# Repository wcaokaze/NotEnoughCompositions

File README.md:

Not Enough Compositions
================================================================================

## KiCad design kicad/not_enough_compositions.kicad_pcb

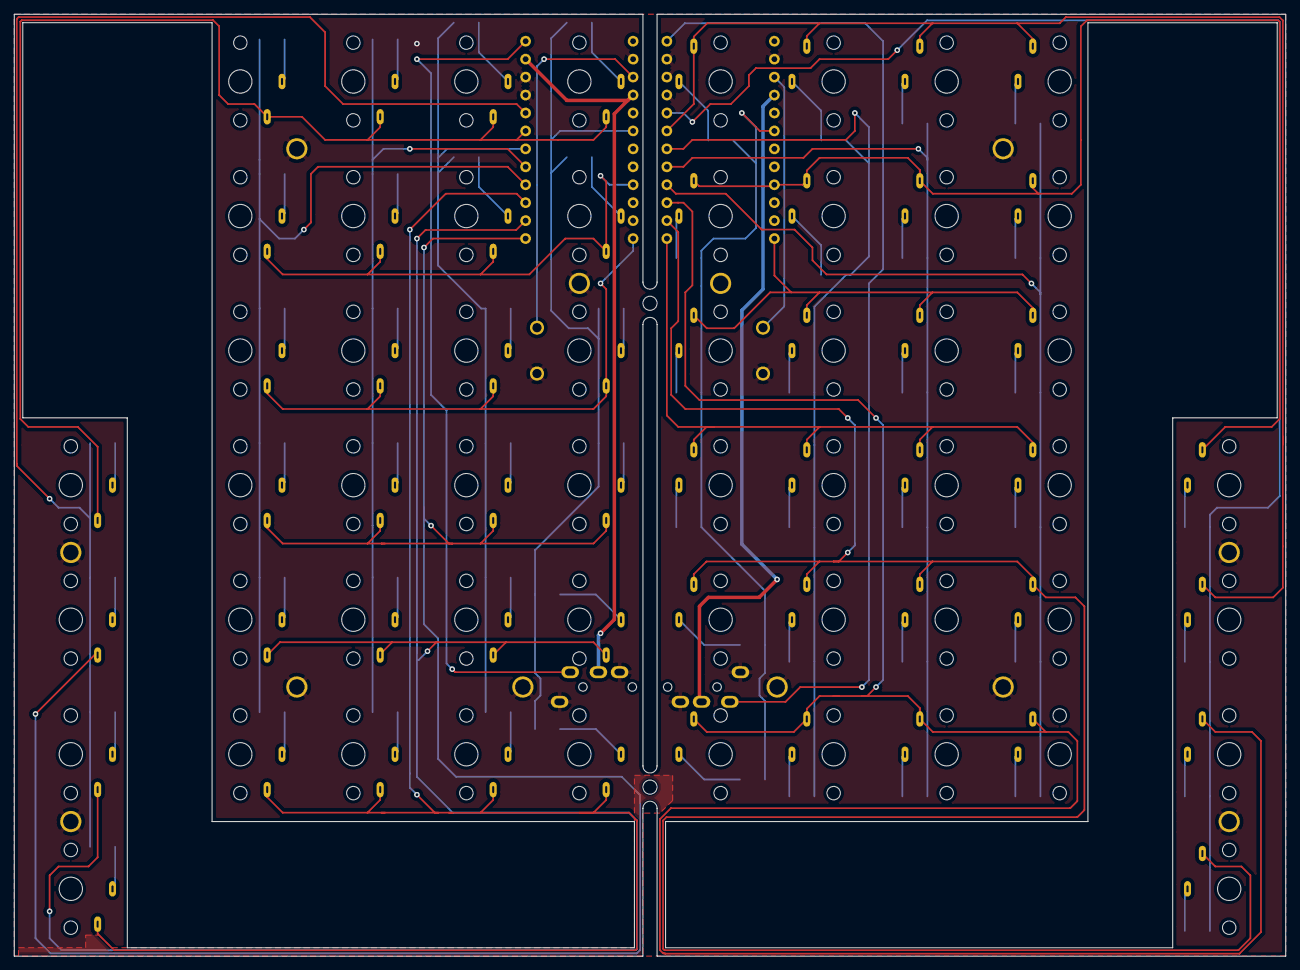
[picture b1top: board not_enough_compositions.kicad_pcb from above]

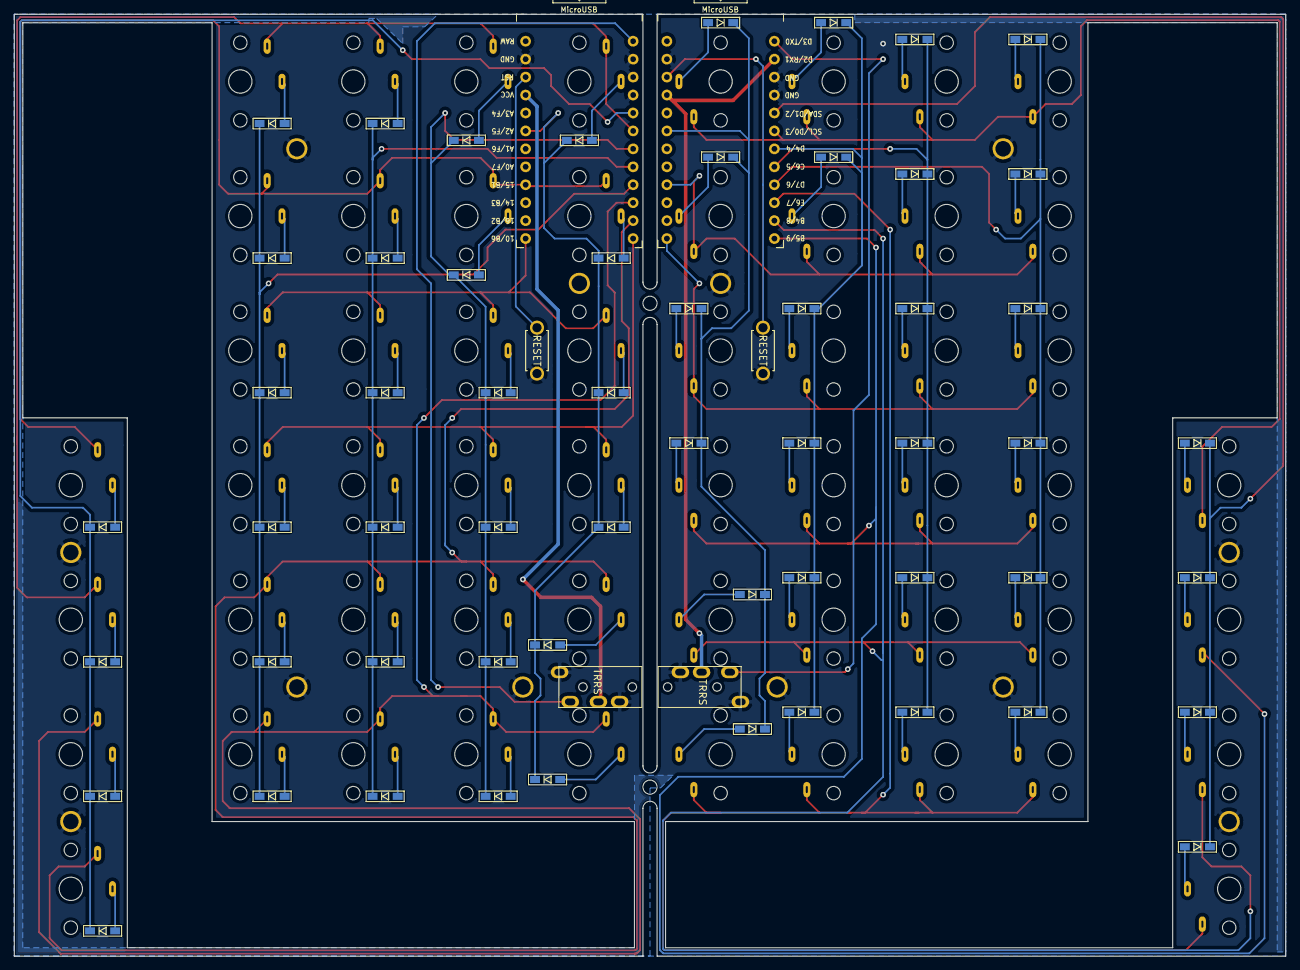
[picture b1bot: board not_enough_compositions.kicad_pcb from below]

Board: 2 copper layers, 180.0 x 133.3 mm, 118 parts (62 on the bottom side), 85 nets.

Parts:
D1, D2, D3, D4, D5, D6, D7, D8, D9, D10, D11, D12, D13, D14, D15, D16, D17, D18, D19, D20, D21, D22, D23, D24, D25, D26, D27, D28, D29, D30, D31, D32, D33, D34, D35, D36, D37, D38, D39, D40, D41, D42, D43, D44, D45, D46, D47, D48, D49, D50, D51, D52, D53, D54, D55, D56: D; D3_SMD_v2
J1, J2: MJ-4PP-9; MJ-4PP-9_1side
SW1, SW2: SW_PUSH; ResetSW_1side
SW3, SW4, SW5, SW6, SW7, SW8, SW9, SW10, SW11, SW12, SW13, SW14, SW15, SW16, SW17, SW18, SW19, SW20, SW21, SW22, SW23, SW24, SW25, SW26, SW27, SW28, SW29, SW30, SW31, SW32, SW33, SW34, SW35, SW36, SW37, SW38, SW39, SW40, SW41, SW42, SW43, SW44, SW45, SW46, SW47, SW48, SW49, SW50, SW51, SW52, SW53, SW54, SW55, SW56, SW57, SW58: SW_PUSH; choc_v1
U1, U2: ProMicro; ProMicro_v3.5

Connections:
GND: J1.A, J1.B, J2.A, J2.B, SW1.2, SW2.1, U1.3, U1.4, U1.23, U2.2, U2.3, U2.4, U2.23
unnamed: D1.2, SW3.2
unnamed: D2.2, SW4.2
unnamed: D3.2, SW5.2
unnamed: D4.2, SW6.2
unnamed: D5.2, SW7.2
unnamed: D6.2, SW8.2
unnamed: D7.2, SW9.2
unnamed: D8.2, SW10.2
unnamed: D9.2, SW11.2
unnamed: D10.2, SW12.2
unnamed: D11.2, SW13.2
unnamed: D12.2, SW14.2
unnamed: D13.2, SW15.2
unnamed: D14.2, SW16.2
unnamed: D15.2, SW17.2
unnamed: D16.2, SW18.2
unnamed: D17.2, SW19.2
unnamed: D18.2, SW20.2
unnamed: D19.2, SW21.2
unnamed: D20.2, SW22.2
unnamed: D21.2, SW23.2
unnamed: D22.2, SW24.2
unnamed: D23.2, SW25.2
unnamed: D24.2, SW26.2
unnamed: D25.2, SW27.2
unnamed: D26.2, SW28.2
unnamed: D27.2, SW29.2
unnamed: D28.2, SW30.2
unnamed: D29.2, SW31.2
unnamed: D30.2, SW32.2
unnamed: D31.2, SW33.2
unnamed: D32.2, SW34.2
unnamed: D33.2, SW35.2
unnamed: D34.2, SW36.2
unnamed: D35.2, SW37.2
unnamed: D36.2, SW38.2
unnamed: D37.2, SW39.2
unnamed: D38.2, SW40.2
unnamed: D39.2, SW41.2
unnamed: D40.2, SW42.2
unnamed: D41.2, SW43.2
unnamed: D42.2, SW44.2
unnamed: D43.2, SW45.2
unnamed: D44.2, SW46.2
unnamed: D45.2, SW47.2
unnamed: D46.2, SW48.2
unnamed: D47.2, SW49.2
unnamed: D48.2, SW50.2
unnamed: D49.2, SW51.2
unnamed: D50.2, SW52.2
unnamed: D51.2, SW53.2
unnamed: D52.2, SW54.2
unnamed: D53.2, SW55.2
unnamed: D54.2, SW56.2
unnamed: D55.2, SW57.2
unnamed: D56.2, SW58.2
l_VCC: J1.C, U1.2, U1.21
l_col0: SW3.1, SW15.1, SW27.1, SW39.1, SW51.1, U1.6
l_col1: SW4.1, SW16.1, SW28.1, SW40.1, U1.16
l_col2: SW5.1, SW17.1, SW29.1, SW41.1, U1.13
l_col3: SW6.1, SW18.1, SW30.1, SW42.1, SW52.1, U1.12
l_col4: SW7.1, SW19.1, SW31.1, SW43.1, SW53.1, U1.11
l_col5: SW8.1, SW20.1, SW32.1, SW44.1, SW54.1, U1.10
l_data: J1.D, U1.1
l_reset: SW1.1, U1.22
l_row0: D1.1, D2.1, D3.1, D4.1, D5.1, D6.1, U1.19
l_row1: D13.1, D14.1, D15.1, D16.1, D17.1, D18.1, U1.7
l_row2: D25.1, D26.1, D27.1, D28.1, D29.1, D30.1, U1.8
l_row3: D37.1, D38.1, D39.1, D40.1, D41.1, D42.1, U1.9
l_row4: D49.1, D50.1, D51.1, D52.1, U1.5
r_VCC: J2.C, U2.21
r_col0: SW14.1, SW26.1, SW38.1, SW50.1, SW58.1, U2.6
r_col1: SW13.1, SW25.1, SW37.1, SW49.1, SW57.1, U2.16
r_col2: SW12.1, SW24.1, SW36.1, SW48.1, U2.13
r_col3: SW11.1, SW23.1, SW35.1, SW47.1, U2.12
r_col4: SW10.1, SW22.1, SW34.1, SW46.1, SW56.1, U2.11
r_col5: SW9.1, SW21.1, SW33.1, SW45.1, SW55.1, U2.10
r_data: J2.D, U2.1
r_reset: SW2.2, U2.22
r_row0: D7.1, D8.1, D9.1, D10.1, D11.1, D12.1, U2.19
r_row1: D19.1, D20.1, D21.1, D22.1, D23.1, D24.1, U2.7
r_row2: D31.1, D32.1, D33.1, D34.1, D35.1, D36.1, U2.8
r_row3: D43.1, D44.1, D45.1, D46.1, D47.1, D48.1, U2.9
r_row4: D53.1, D54.1, D55.1, D56.1, U2.5

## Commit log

2021-03-26 デザイン草案
2021-03-26 Kicadプロジェクト作成
2021-03-26 foostan/kbdをサブモジュールに追加
2021-03-26 kbd.libをKicadのシンボルに追加
2021-03-27 回路図を作成
2021-03-27 Choc V2のフットプリントを作成
2021-03-27 ネットリストを生成
2021-03-27 Choc V2のフットプリントの縦サイズを16mmに変更
2021-03-27 Choc V1のフットプリント追加
2021-04-10 基板を作成
2021-04-10 基板の3Dモデルを作成
2021-04-10 底面のゴム板を作成
2021-04-10 ProMicro用のスペースを確保
2021-04-10 はんだ用の空間を設けました
2021-04-10 ダイオードの空間を確保
2021-04-10 renamed: base => alphanumeric
2021-04-11 ケース作成
2021-04-12 ネジ用の穴あけます
2021-04-17 ケース余白の透明部分を作成
2021-04-18 case_margin_topとcase_margin_bottomの間に基板1枚分の隙間ができていたのを修正
2021-04-22 透明部分にネジを挿せるようにネジ穴までの橋を作った
2021-04-29 キーキャップの端に浅めの壁をつけた、それに伴いケースを広めにしないといけなくなったのでした
2021-04-29 screw_bridgeを厚くした
2021-04-29 ゴム足に開けるネジ穴が回転してなかったのを修正
2021-04-29 各パーツを回転してない状態にしておきます
2021-04-30 パーツごとに出せるscadファイルを用意
2021-04-30 choc V1の足だいぶきつかったので穴広くしました
2021-05-05 screw_bridgeを太くした
2021-05-05 親指のscrew_bridgeがなくなったので命名からalphanumericを削除
2021-05-05 chocの足の下に0.2mmの余裕を持たせていたのですがどうやら実物の足はデータシートの値よりかなり短いみたいなので0.2mm詰めます
2021-05-08 ゴム足の左右短くした
2021-05-08 リセットスイッチとTRRSジャックの穴を開けました
2021-05-08 margin_topにキースイッチを通す用の穴開けました
2021-05-09 ProMicroが思ったより高さ必要っぽいので0.5mm高くしました
2021-05-09 キーキャップに足をつけた
2021-05-09 diode_positionが必要なmoduleは引数にdiode_positionsをとるようにした
2021-05-09 renamed: {_ => left_}diode_positions
2021-05-09 右手用出力できるようにした
2021-05-10 各パーツ別出力の配置を再度調整
2021-05-10 case_margin_topがProMicroの足に当たりそうだったので穴あけます
2021-05-10 全体的にネジ穴キツいので0.2mm太くします
2021-05-10 case_margin_topに親指側キースイッチの穴がなかったのであけました
2021-05-10 キーキャップ出力用scadファイル追加
2021-05-10 キーキャップの北側の壁を生成するとサイズが狂うのを修正
2021-05-12 margin_topの左端の橋を削除
2021-05-12 margin_bottomが両方右手用になっていたのを修正
2021-05-13 ねじの山が最後まで入り切らないので頭部分の穴をすこし広くします
2021-05-13 ネジの実物の長さ測ったら8mmもなかったです
2021-05-14 margin_topのTRRSコネクタが当たる部分を取り除きました
2021-05-16 まあキー間0.4mmは無理ありましたよねプリンタの精度的にもchocのグラつき的にも
2021-05-16 ProMicroのはんだの盛りが思ったより高いので傾きをキツくします
2021-05-16 傾きを変えた影響で出力用モデルが衝突していたので余白を再調整しました
2021-05-16 傾きを変えた影響でリセットスイッチの穴が貫通しなくなっていたのを修正
2021-05-16 PCB出力ファイル
2021-05-16 README
2021-05-17 rubber_thumbのキースイッチの穴を貫通させられてなかったのを修正
2021-05-17 stlを出力した
2022-05-16 ビルドガイドを消しました
    べつに要らん情報と思った。READMEにごちゃごちゃ書いてるとかっこよくないし
2022-05-16 写真を追加
